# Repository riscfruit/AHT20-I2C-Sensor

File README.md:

# AHT20-I2C-Sensor
Riscfruit Aosong AHT20 umidity and temperature sensor module

### Software
For Micropython, we recommend [micropython_ahtx0](https://github.com/targetblank/micropython_ahtx0)

### Gallery

### License
Copyright (c) 2026, Riscfruit Laboratory. This open source hardware is released under [CERN-OHL-S-2.0](LICENSE).

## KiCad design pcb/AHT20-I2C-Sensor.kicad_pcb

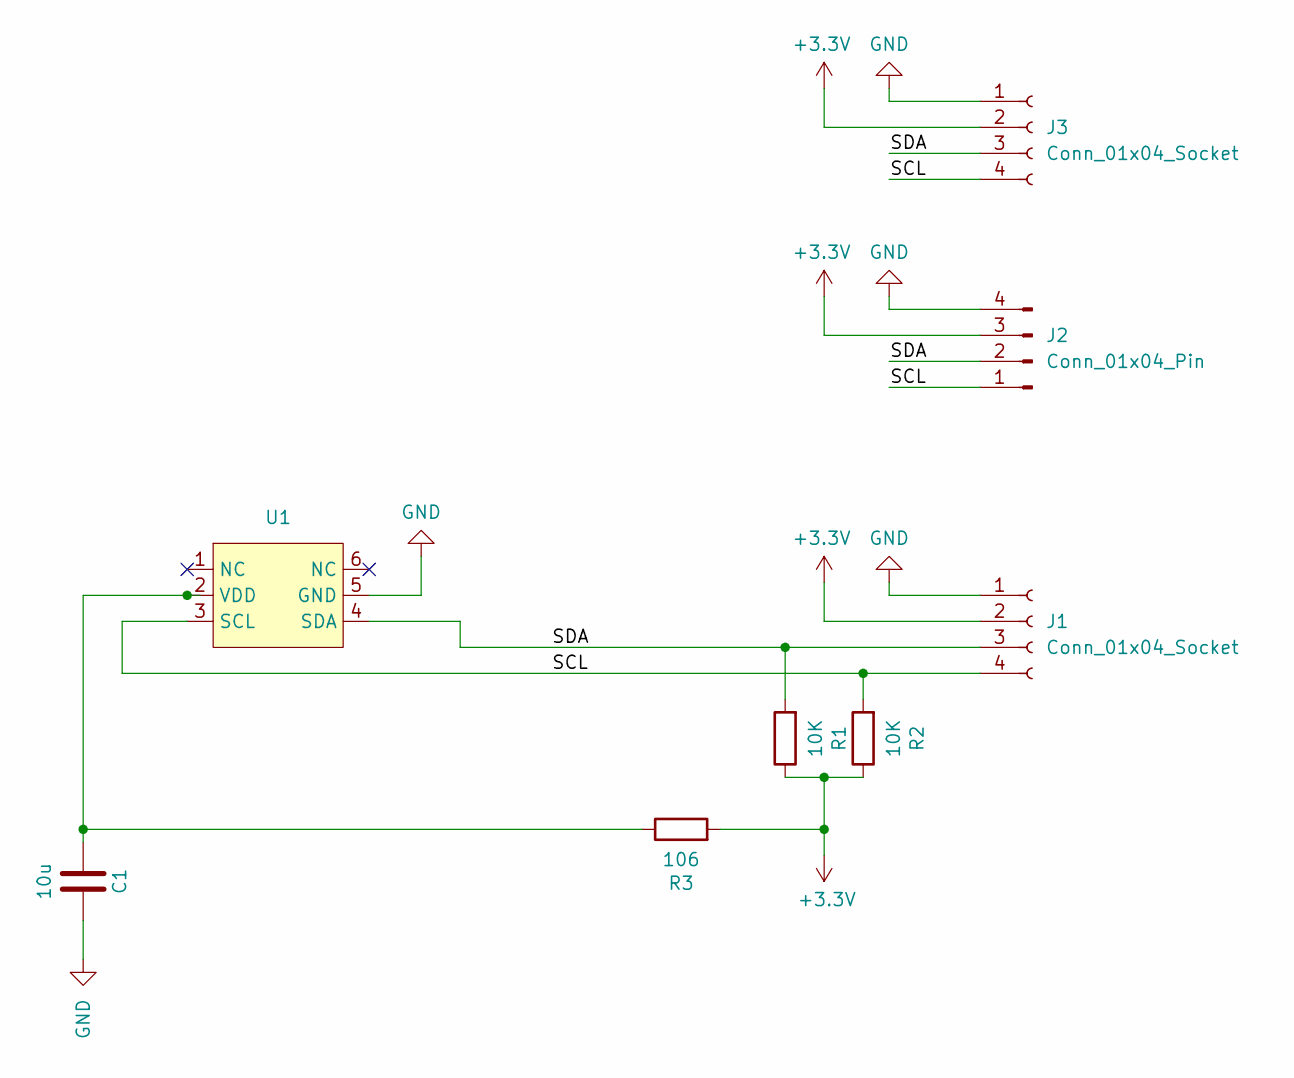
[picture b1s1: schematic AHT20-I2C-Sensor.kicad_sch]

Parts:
C1: 10u; C_0402_1005Metric
J1, J3: Conn_01x04_Socket; JST_SH_SM04B-SRSS-TB_1x04-1MP_P1.00mm_Horizontal
J2: Conn_01x04_Pin; PinHeader_1x04_P2.54mm_Vertical
R1, R2: 10K; R_0402_1005Metric
R3: 106; R_0402_1005Metric
U1: SENSOR-SMD_L3.0-W3.0-P1.00-BR

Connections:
+3.3V: J1.2, J2.3, J3.2, R1.1, R2.1, R3.2
/SCL: J1.4, J2.1, J3.4, R2.2, U1.3 (SCL)
/SDA: J1.3, J2.2, J3.3, R1.2, U1.4 (SDA)
GND: C1.2, J1.1, J2.4, J3.1, U1.5 (GND)
unnamed: C1.1, R3.1, U1.2 (VDD)

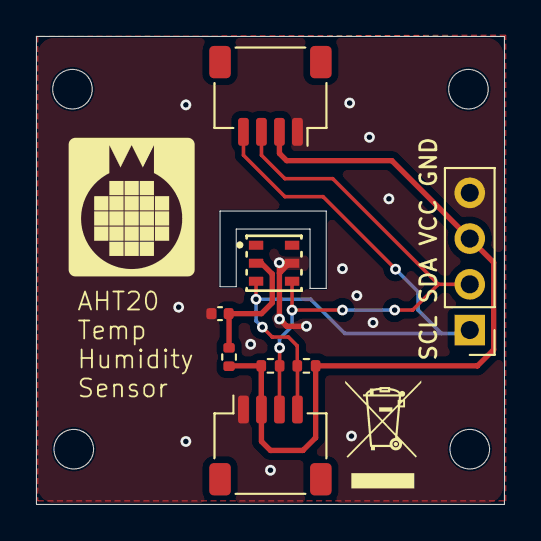
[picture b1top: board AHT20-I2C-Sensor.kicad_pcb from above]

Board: 2 copper layers, 26.0 x 26.0 mm, 12 parts (0 on the bottom side), 5 nets.

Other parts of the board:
H1, H1#2, H1#3, H1#4: MountingHole; MountingHole_2.2mm_M2
